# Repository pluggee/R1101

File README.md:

# R1101
particle.io photon Interposer

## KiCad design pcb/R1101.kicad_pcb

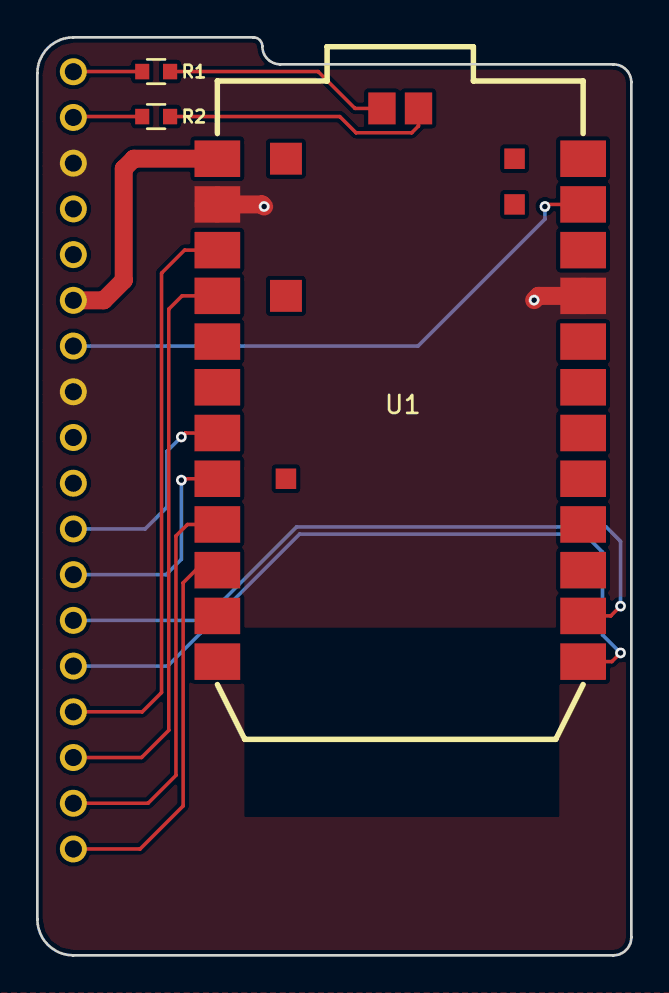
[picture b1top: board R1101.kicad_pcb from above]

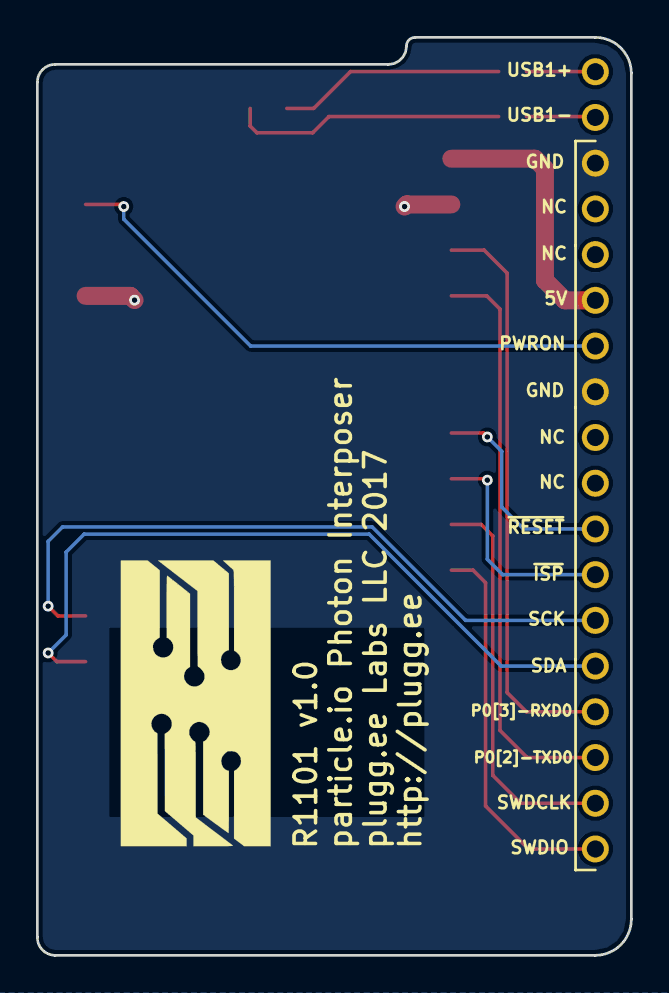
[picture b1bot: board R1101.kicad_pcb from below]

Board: 2 copper layers, 33.0 x 51.0 mm, 5 parts (2 on the bottom side), 15 nets.

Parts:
A1: ART; pluggeeLabsIcon-16X8
J1: COMPUTE_MOD_1
R1, R2: RC0603FR-070RL; RESC0603
U1: PHOTON_SMD

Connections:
/5V: J1.4, U1.1
/SCK: J1.11, U1.14
/SDA: J1.12, U1.13
/SWDCLK: J1.15, U1.9
/SWDIO: J1.16, U1.10
/SYSRXD0-PHOTONTX: J1.13, U1.3
/SYSTXD0-PHOTONRX: J1.14, U1.4
/USB+: J1.18, R1.1
/USB-: J1.17, R2.1
/pUSB+: R1.2, U1.31
/pUSB-: R2.2, U1.30
/~ISP: J1.10, U1.8
/~RESET: J1.9, U1.7
/~RST: J1.5, U1.23
GND: J1.1, J1.6, U1.2, U1.21

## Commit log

2017-04-03 added silkscreen art
2017-04-04 connected I2C
2017-04-06 updated SWD signal naming
